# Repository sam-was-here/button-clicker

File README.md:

# Button Clicker

This repository contains the project files for an electronic button clicker. A button clicker is a small electronic device that counts how many times the button on the device has been pressed. It features an additional button that displays the count on the device to save battery power. The maximum count on the device is 999,999, and it has a button debounce time of approximately 10ms. The counting mechanism utilizes BCD counters, and the count is displayed on 7-segment displays using a BCD to 7-segment IC. The device itself has dimensions of approximately 4 x 1 x 0.65 inches and comes with a 3D-printed case designed to hold the PCB. The PCB is a 2-layered board with a trace width and spacing of 0.15mm. Most components are surface mount devices (SMD), except for the buttons and displays. To ensure accurate functionality, it is recommended to add shielding inside the case; otherwise, the button clicker may randomly count up, reset, or count down. The electronics design was created using KiCad, while the case was made using FreeCAD. All design files are included in the repository, allowing for modifications if desired.

## Images

## Bill of Materials (BOM)

- BT1: 3034TR - CR2032 battery holder - [Digi-Key Link](https://www.digikey.com/short/wqhf8fbf)
- C1-C11: 0603 0.1uF ceramic capacitor - bypass capacitor
- D1: SOD-523 - Crowbar diode for reverse polarity protection
- D2-D5: SMA - TVS diode - [Mouser Link](https://mou.sr/43r05RL)
- R1-R5: 0603 100k 5% resistor - button pull-up/down resistors and debouncing
- R6-R47: 0603 1k 5% resistor - LED current limiting resistors
- SW1: THT tack switch right angle - button for counting clicks - [Mouser Link](https://mou.sr/42t1Exi)
- SW2: THT tack switch right angle - button to light up display - [Mouser Link](https://mou.sr/42t1Exi)
- SW3: SMD tack switch - reset button - [Mouser Link](https://mou.sr/3oV6upt)
- U1: SOT-23 (5) 74LVC1G17 - Single Schmitt-Trigger Buffer - [Digi-Key Link](https://www.digikey.com/short/7bh4nv4q)
- U2-U4: TSSOP-16 74HC390 - Dual Decade RPL Counter - [Mouser Link](https://mou.sr/3katv4U)
- U5-U10: TSSOP-16 74HC4511 - BCD-to-7 Segment - [Digi-Key Link](https://www.digikey.com/short/bz3pz8r9)
- U11-U16: INND-TS30RCB - Red 7-segment display - [Digi-Key Link](https://www.digikey.com/short/40qw31cv)

## Schematic

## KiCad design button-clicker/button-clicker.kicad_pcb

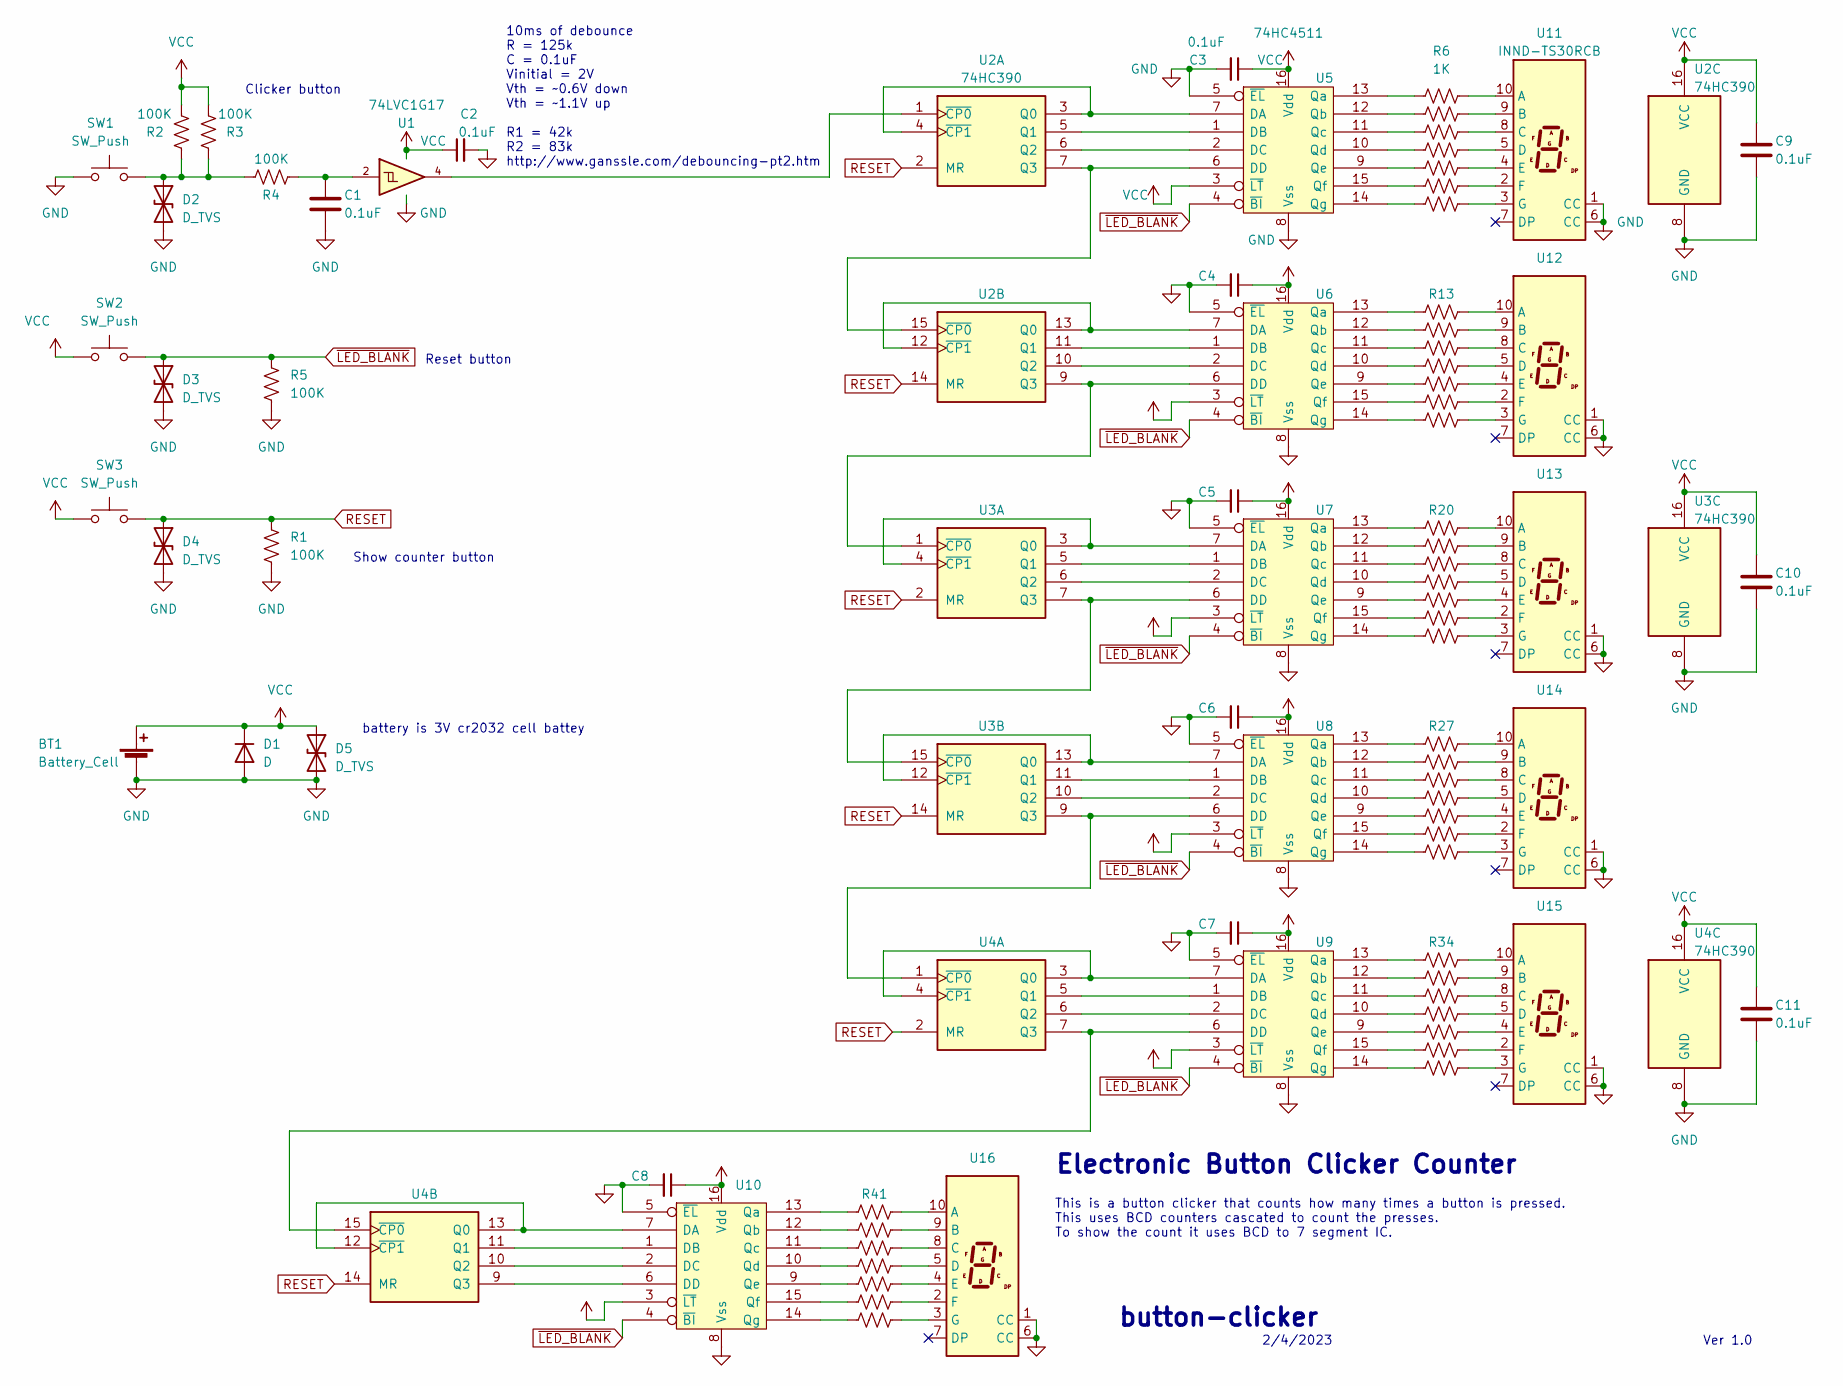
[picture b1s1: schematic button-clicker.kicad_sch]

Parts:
BT1: Battery_Cell; BatteryHolder_Keystone_3034_1x20mm
C1, C2, C3, C4, C5, C6, C7, C8, C9, C10, C11: 0.1uF; C_0603_1608Metric; JLC 0603
D1: D; D_SMA
D2, D3, D4, D5: D_TVS; D_SOD-523
R1, R2, R3, R4, R5: 100K; R_0603_1608Metric; JLC 0603
R6, R7, R8, R9, R10, R11, R12, R13, R14, R15, R16, R17, R18, R19, R20, R21, R22, R23, R24, R25, R26, R27, R28, R29, R30, R31, R32, R33, R34, R35, R36, R37, R38, R39, R40, R41, R42, R43, R44, R45, R46, R47: 1K; R_0603_1608Metric; JLC 0603
SW1: SW_Push; SW_Tactile_SPST_Angled_PTS645Vx83-2LFS
SW2: SW_Push; SW_Tactile_SPST_Angled_PTS645Vx39-2LFS
SW3: SW_Push; SW_Push_1P1T_NO_Vertical_Wuerth_434133025816
U1: 74LVC1G17; SOT-23-5
U2, U3, U4: 74HC390; TSSOP-16_4.4x5mm_P0.65mm
U5, U6, U7, U8, U9, U10: 74HC4511; TSSOP-16_4.4x5mm_P0.65mm
U11, U12, U13, U14, U15, U16: INND-TS30RCB; HDSP-A151

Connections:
GND: BT1.2 (-), C1.2, C2.2, C3.2, C4.2, C5.2, C6.2, C7.2, C8.2, C9.2, C10.2, C11.2, D1.2 (A), D2.2 (A2), D3.2 (A2), D4.2 (A2), D5.2 (A2), R1.2, R5.2, SW1.1, U1.3 (GND), U2.8 (GND), U3.8 (GND), U4.8 (GND), U5.5 (~EL), U5.8 (Vss), U6.5 (~EL), U6.8 (Vss), U7.5 (~EL), U7.8 (Vss), U8.5 (~EL), U8.8 (Vss), U9.5 (~EL), U9.8 (Vss), U10.5 (~EL), U10.8 (Vss), U11.1 (CC), U11.6 (CC), U12.1 (CC), U12.6 (CC), U13.1 (CC), U13.6 (CC), U14.1 (CC), U14.6 (CC), U15.1 (CC), U15.6 (CC), U16.1 (CC), U16.6 (CC)
unnamed: C1.1, R4.2, U1.2
unnamed: D2.1 (A1), R2.2, R3.1, R4.1, SW1.2
unnamed: U2.3 (Q0), U2.4 (~CP1), U5.7 (DA)
unnamed: U2.5 (Q1), U5.1 (DB)
unnamed: U2.6 (Q2), U5.2 (DC)
unnamed: U2.7 (Q3), U2.15 (~CP0), U5.6 (DD)
unnamed: U1.4, U2.1 (~CP0)
unnamed: U2.12 (~CP1), U2.13 (Q0), U6.7 (DA)
unnamed: U2.11 (Q1), U6.1 (DB)
unnamed: U2.10 (Q2), U6.2 (DC)
unnamed: U2.9 (Q3), U3.1 (~CP0), U6.6 (DD)
unnamed: U3.3 (Q0), U3.4 (~CP1), U7.7 (DA)
unnamed: U3.5 (Q1), U7.1 (DB)
unnamed: U3.6 (Q2), U7.2 (DC)
unnamed: U3.7 (Q3), U3.15 (~CP0), U7.6 (DD)
unnamed: U3.12 (~CP1), U3.13 (Q0), U8.7 (DA)
unnamed: U3.11 (Q1), U8.1 (DB)
unnamed: U3.10 (Q2), U8.2 (DC)
unnamed: U3.9 (Q3), U4.1 (~CP0), U8.6 (DD)
unnamed: U4.3 (Q0), U4.4 (~CP1), U9.7 (DA)
unnamed: U4.5 (Q1), U9.1 (DB)
unnamed: U4.6 (Q2), U9.2 (DC)
unnamed: U4.7 (Q3), U4.15 (~CP0), U9.6 (DD)
unnamed: R6.1, U5.13 (Qa)
unnamed: R7.1, U5.12 (Qb)
unnamed: R8.1, U5.11 (Qc)
unnamed: R9.1, U5.10 (Qd)
unnamed: R10.1, U5.9 (Qe)
unnamed: R11.1, U5.15 (Qf)
unnamed: R12.1, U5.14 (Qg)
unnamed: R13.1, U6.13 (Qa)
unnamed: R14.1, U6.12 (Qb)
unnamed: R15.1, U6.11 (Qc)
unnamed: R16.1, U6.10 (Qd)
unnamed: R17.1, U6.9 (Qe)
unnamed: R18.1, U6.15 (Qf)
unnamed: R19.1, U6.14 (Qg)
unnamed: R20.1, U7.13 (Qa)
unnamed: R21.1, U7.12 (Qb)
unnamed: R22.1, U7.11 (Qc)
unnamed: R23.1, U7.10 (Qd)
unnamed: R24.1, U7.9 (Qe)
unnamed: R25.1, U7.15 (Qf)
unnamed: R26.1, U7.14 (Qg)
unnamed: R27.1, U8.13 (Qa)
unnamed: R28.1, U8.12 (Qb)
unnamed: R29.1, U8.11 (Qc)
unnamed: R30.1, U8.10 (Qd)
unnamed: R31.1, U8.9 (Qe)
unnamed: R32.1, U8.15 (Qf)
unnamed: R33.1, U8.14 (Qg)
unnamed: R34.1, U9.13 (Qa)
unnamed: R35.1, U9.12 (Qb)
unnamed: R36.1, U9.11 (Qc)
unnamed: R37.1, U9.10 (Qd)
unnamed: R38.1, U9.9 (Qe)
unnamed: R39.1, U9.15 (Qf)
unnamed: R40.1, U9.14 (Qg)
unnamed: U4.12 (~CP1), U4.13 (Q0), U10.7 (DA)
unnamed: U4.11 (Q1), U10.1 (DB)
unnamed: U4.10 (Q2), U10.2 (DC)
unnamed: U4.9 (Q3), U10.6 (DD)
unnamed: R41.1, U10.13 (Qa)
unnamed: R42.1, U10.12 (Qb)
unnamed: R43.1, U10.11 (Qc)
unnamed: R44.1, U10.10 (Qd)
unnamed: R45.1, U10.9 (Qe)
unnamed: R46.1, U10.15 (Qf)
unnamed: R47.1, U10.14 (Qg)
unnamed: R6.2, U11.10 (A)
unnamed: R7.2, U11.9 (B)
unnamed: R8.2, U11.8 (C)
unnamed: R9.2, U11.5 (D)
unnamed: R10.2, U11.4 (E)
unnamed: R11.2, U11.2 (F)
unnamed: R12.2, U11.3 (G)
unnamed: R13.2, U12.10 (A)
unnamed: R14.2, U12.9 (B)
unnamed: R15.2, U12.8 (C)
unnamed: R16.2, U12.5 (D)
unnamed: R17.2, U12.4 (E)
unnamed: R18.2, U12.2 (F)
unnamed: R19.2, U12.3 (G)
unnamed: R20.2, U13.10 (A)
unnamed: R21.2, U13.9 (B)
unnamed: R22.2, U13.8 (C)
unnamed: R23.2, U13.5 (D)
unnamed: R24.2, U13.4 (E)
unnamed: R25.2, U13.2 (F)
unnamed: R26.2, U13.3 (G)
unnamed: R27.2, U14.10 (A)
unnamed: R28.2, U14.9 (B)
unnamed: R29.2, U14.8 (C)
unnamed: R30.2, U14.5 (D)
unnamed: R31.2, U14.4 (E)
unnamed: R32.2, U14.2 (F)
unnamed: R33.2, U14.3 (G)
unnamed: R34.2, U15.10 (A)
unnamed: R35.2, U15.9 (B)
unnamed: R36.2, U15.8 (C)
unnamed: R37.2, U15.5 (D)
unnamed: R38.2, U15.4 (E)
unnamed: R39.2, U15.2 (F)
unnamed: R40.2, U15.3 (G)
unnamed: R41.2, U16.10 (A)
unnamed: R42.2, U16.9 (B)
unnamed: R43.2, U16.8 (C)
unnamed: R44.2, U16.5 (D)
unnamed: R45.2, U16.4 (E)
unnamed: R46.2, U16.2 (F)
unnamed: R47.2, U16.3 (G)
RESET: D4.1 (A1), R1.1, SW3.2, U2.2 (MR), U2.14 (MR), U3.2 (MR), U3.14 (MR), U4.2 (MR), U4.14 (MR)
VCC: BT1.1 (+), C2.1, C3.1, C4.1, C5.1, C6.1, C7.1, C8.1, C9.1, C10.1, C11.1, D1.1 (K), D5.1 (A1), R2.1, R3.2, SW2.1, SW3.1, U1.5 (VCC), U2.16 (VCC), U3.16 (VCC), U4.16 (VCC), U5.3 (~LT), U5.16 (Vdd), U6.3 (~LT), U6.16 (Vdd), U7.3 (~LT), U7.16 (Vdd), U8.3 (~LT), U8.16 (Vdd), U9.3 (~LT), U9.16 (Vdd), U10.3 (~LT), U10.16 (Vdd)
~LED_BLANK: D3.1 (A1), R5.1, SW2.2, U5.4 (~BI), U6.4 (~BI), U7.4 (~BI), U8.4 (~BI), U9.4 (~BI), U10.4 (~BI)

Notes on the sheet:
Clicker button
button-clicker
10ms of debounce R = 125k C = 0.1uF Vinitial = 2V Vth = ~0.6V down Vth = ~1.1V up R1 = 42k R2 = 83k http://www.ganssle.com/debouncing-pt2.htm
This is a button clicker that counts how many times a button is pressed. This uses BCD counters cascated to count the presses. To show the count it uses BCD to 7 segment IC.
Reset button
Electronic Button Clicker Counter
battery is 3V cr2032 cell battey
2/4/2023
Show counter button
Ver 1.0

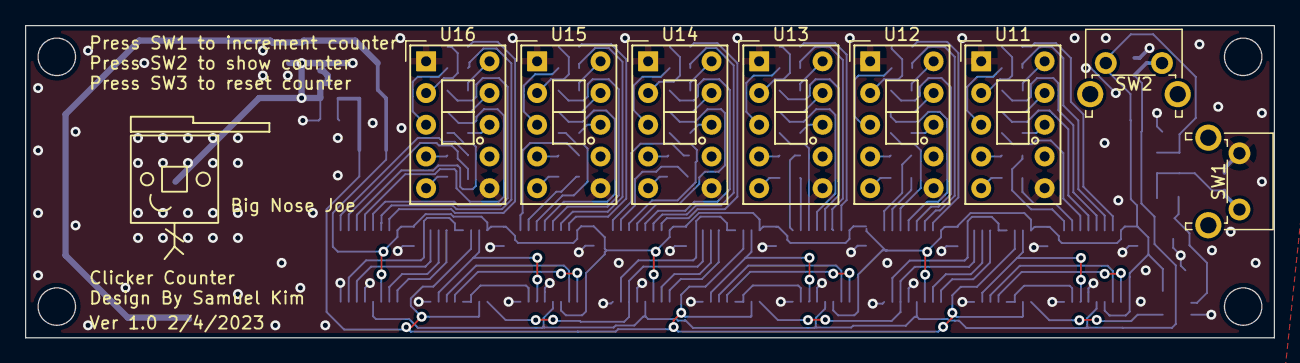
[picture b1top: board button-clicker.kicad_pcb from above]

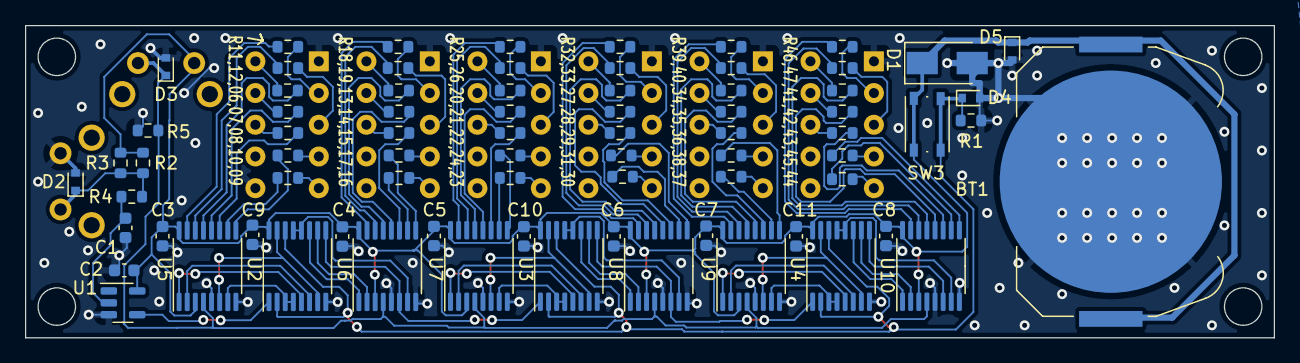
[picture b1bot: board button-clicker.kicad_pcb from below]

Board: 2 copper layers, 100.0 x 25.0 mm, 83 parts (75 on the bottom side), 115 nets.
